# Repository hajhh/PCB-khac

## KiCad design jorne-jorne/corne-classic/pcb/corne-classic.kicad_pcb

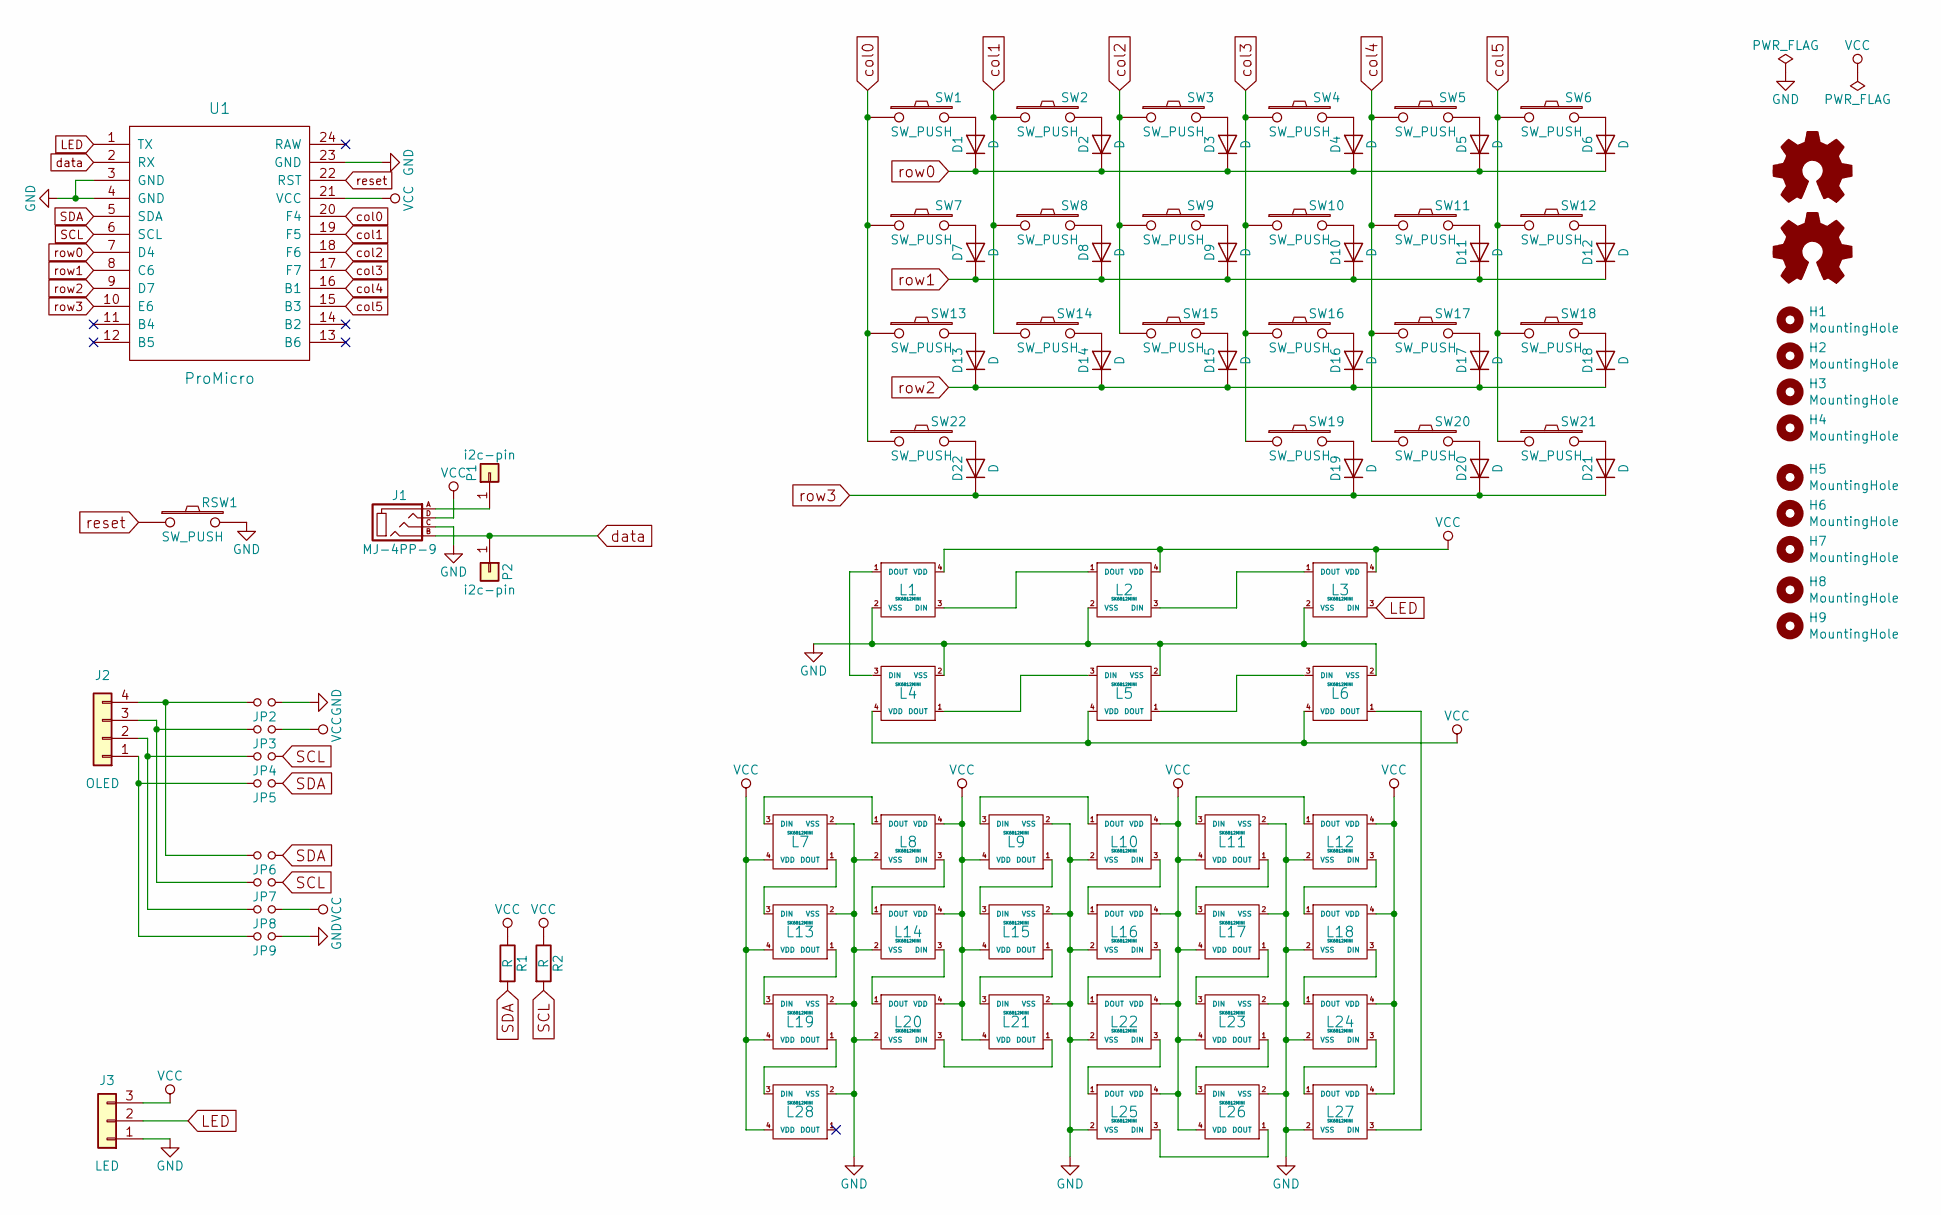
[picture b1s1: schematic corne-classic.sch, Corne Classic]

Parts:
D1, D2, D3, D4, D5, D6, D7, D8, D9, D10, D11, D12, D13, D14, D15, D16, D17, D18, D19, D20, D21, D22: D; D3_TH_SMD
G1, G2: Logo_Open_Hardware_Small; corne
H1, H2, H3, H4, H5, H6, H7, H8, H9: MountingHole; LEGO_HOLE
J1: MJ-4PP-9
J2: OLED
J3: LED; StripLED_rev
JP2, JP3, JP4, JP5, JP6, JP7, JP8, JP9: Jumper
L1, L2, L3, L4, L5, L6: SK6812MINI; SK6812MINI_underglow
L7, L8, L9, L10, L11, L12, L13, L14, L15, L16, L17, L18, L19, L20, L21, L22, L23, L24, L25, L26, L27, L28: SK6812MINI; SK6812MINI_rev
P1, P2: i2c-pin; 1pin_conn
R1, R2: R
RSW1: SW_PUSH; ResetSW
SW1, SW2, SW3, SW4, SW5, SW6, SW7, SW8, SW9, SW10, SW11, SW12, SW13, SW14, SW15, SW16, SW17, SW18, SW19, SW20, SW22: SW_PUSH; MX_ALPS_PG1350_noLed
SW21: SW_PUSH; MX_ALPS_PG1350_noLed_1.75u
U1: ProMicro; ProMicro_v2

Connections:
GND: J1.C, J3.1, JP2.1, JP9.1, L1.2 (VSS), L2.2 (VSS), L3.2 (VSS), L4.2 (VSS), L5.2 (VSS), L6.2 (VSS), L7.2 (VSS), L8.2 (VSS), L9.2 (VSS), L10.2 (VSS), L11.2 (VSS), L12.2 (VSS), L13.2 (VSS), L14.2 (VSS), L15.2 (VSS), L16.2 (VSS), L17.2 (VSS), L18.2 (VSS), L19.2 (VSS), L20.2 (VSS), L21.2 (VSS), L22.2 (VSS), L23.2 (VSS), L24.2 (VSS), L25.2 (VSS), L26.2 (VSS), L27.2 (VSS), L28.2 (VSS), RSW1.2, U1.3 (GND), U1.4 (GND), U1.23 (GND)
LED: J3.2, L3.3 (DIN), U1.1 (TX)
unnamed: D1.2 (A), SW1.2
unnamed: D2.2 (A), SW2.2
unnamed: D3.2 (A), SW3.2
unnamed: D4.2 (A), SW4.2
unnamed: D5.2 (A), SW5.2
unnamed: D6.2 (A), SW6.2
unnamed: D7.2 (A), SW7.2
unnamed: D8.2 (A), SW8.2
unnamed: D9.2 (A), SW9.2
unnamed: D10.2 (A), SW10.2
unnamed: D11.2 (A), SW11.2
unnamed: D12.2 (A), SW12.2
unnamed: D13.2 (A), SW13.2
unnamed: D14.2 (A), SW14.2
unnamed: D15.2 (A), SW15.2
unnamed: D16.2 (A), SW16.2
unnamed: D17.2 (A), SW17.2
unnamed: D18.2 (A), SW18.2
unnamed: D19.2 (A), SW19.2
unnamed: D20.2 (A), SW20.2
unnamed: D21.2 (A), SW21.2
unnamed: D22.2 (A), SW22.2
unnamed: J1.A, P1.1
unnamed: J2.1, JP5.2, JP9.2
unnamed: J2.2, JP4.2, JP8.2
unnamed: J2.3, JP3.2, JP7.2
unnamed: J2.4, JP2.2, JP6.2
unnamed: L1.1 (DOUT), L4.3 (DIN)
unnamed: L1.3 (DIN), L2.1 (DOUT)
unnamed: L2.3 (DIN), L3.1 (DOUT)
unnamed: L4.1 (DOUT), L5.3 (DIN)
unnamed: L5.1 (DOUT), L6.3 (DIN)
unnamed: L7.3 (DIN), L8.1 (DOUT)
unnamed: L9.3 (DIN), L10.1 (DOUT)
unnamed: L10.3 (DIN), L16.1 (DOUT)
unnamed: L11.1 (DOUT), L17.3 (DIN)
unnamed: L11.3 (DIN), L12.1 (DOUT)
unnamed: L12.3 (DIN), L18.1 (DOUT)
unnamed: L13.1 (DOUT), L19.3 (DIN)
unnamed: L7.1 (DOUT), L13.3 (DIN)
unnamed: L8.3 (DIN), L14.1 (DOUT)
unnamed: L14.3 (DIN), L20.1 (DOUT)
unnamed: L15.1 (DOUT), L21.3 (DIN)
unnamed: L9.1 (DOUT), L15.3 (DIN)
unnamed: L16.3 (DIN), L22.1 (DOUT)
unnamed: L17.1 (DOUT), L23.3 (DIN)
unnamed: L18.3 (DIN), L24.1 (DOUT)
unnamed: L19.1 (DOUT), L28.3 (DIN)
unnamed: L20.3 (DIN), L21.1 (DOUT)
unnamed: L22.3 (DIN), L25.1 (DOUT)
unnamed: L23.1 (DOUT), L26.3 (DIN)
unnamed: L24.3 (DIN), L27.1 (DOUT)
unnamed: L25.3 (DIN), L26.1 (DOUT)
unnamed: L6.1 (DOUT), L27.3 (DIN)
SCL: JP4.1, JP7.1, R2.2, U1.6 (SCL)
SDA: JP5.1, JP6.1, R1.2, U1.5 (SDA)
VCC: J1.D, J3.3, JP3.1, JP8.1, L1.4 (VDD), L2.4 (VDD), L3.4 (VDD), L4.4 (VDD), L5.4 (VDD), L6.4 (VDD), L7.4 (VDD), L8.4 (VDD), L9.4 (VDD), L10.4 (VDD), L11.4 (VDD), L12.4 (VDD), L13.4 (VDD), L14.4 (VDD), L15.4 (VDD), L16.4 (VDD), L17.4 (VDD), L18.4 (VDD), L19.4 (VDD), L20.4 (VDD), L21.4 (VDD), L22.4 (VDD), L23.4 (VDD), L24.4 (VDD), L25.4 (VDD), L26.4 (VDD), L27.4 (VDD), L28.4 (VDD), R1.1, R2.1, U1.21 (VCC)
col0: SW1.1, SW7.1, SW13.1, SW22.1, U1.20 (F4)
col1: SW2.1, SW8.1, SW14.1, U1.19 (F5)
col2: SW3.1, SW9.1, SW15.1, U1.18 (F6)
col3: SW4.1, SW10.1, SW16.1, SW19.1, U1.17 (F7)
col4: SW5.1, SW11.1, SW17.1, SW20.1, U1.16 (B1)
col5: SW6.1, SW12.1, SW18.1, SW21.1, U1.15 (B3)
data: J1.B, P2.1, U1.2 (RX)
reset: RSW1.1, U1.22 (RST)
row0: D1.1 (K), D2.1 (K), D3.1 (K), D4.1 (K), D5.1 (K), D6.1 (K), U1.7 (D4)
row1: D7.1 (K), D8.1 (K), D9.1 (K), D10.1 (K), D11.1 (K), D12.1 (K), U1.8 (C6)
row2: D13.1 (K), D14.1 (K), D15.1 (K), D16.1 (K), D17.1 (K), D18.1 (K), U1.9 (D7)
row3: D19.1 (K), D20.1 (K), D21.1 (K), D22.1 (K), U1.10 (E6)

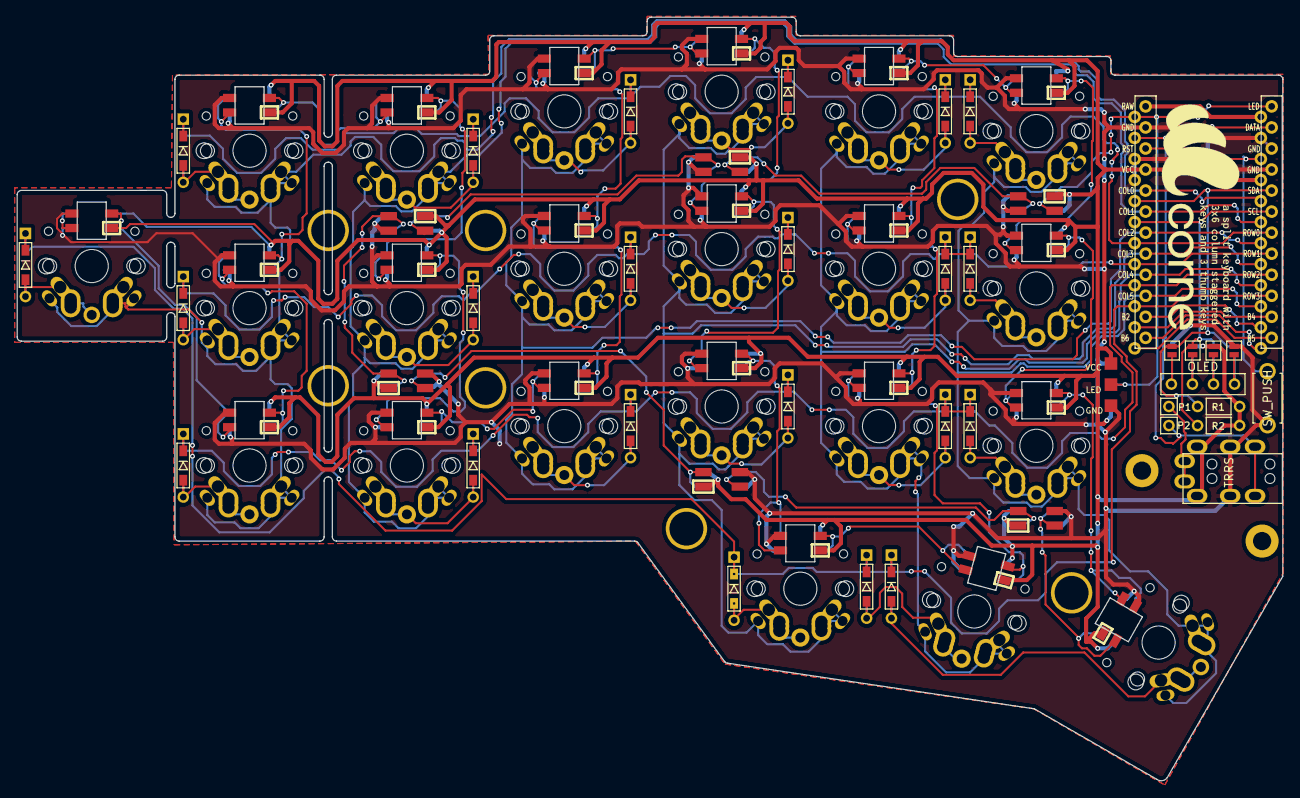
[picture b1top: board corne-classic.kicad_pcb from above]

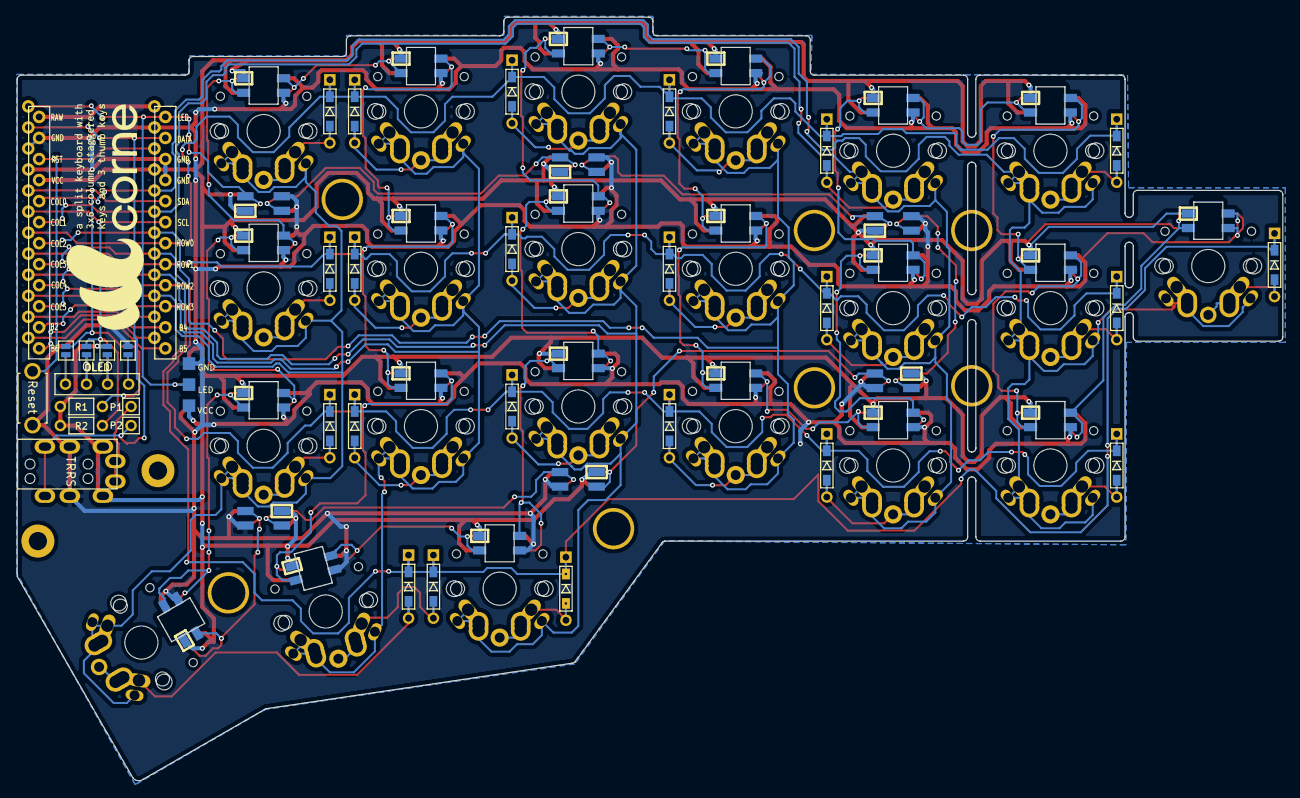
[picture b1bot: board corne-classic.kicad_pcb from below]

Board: 2 copper layers, 152.8 x 92.2 mm, 100 parts (5 on the bottom side), 71 nets.

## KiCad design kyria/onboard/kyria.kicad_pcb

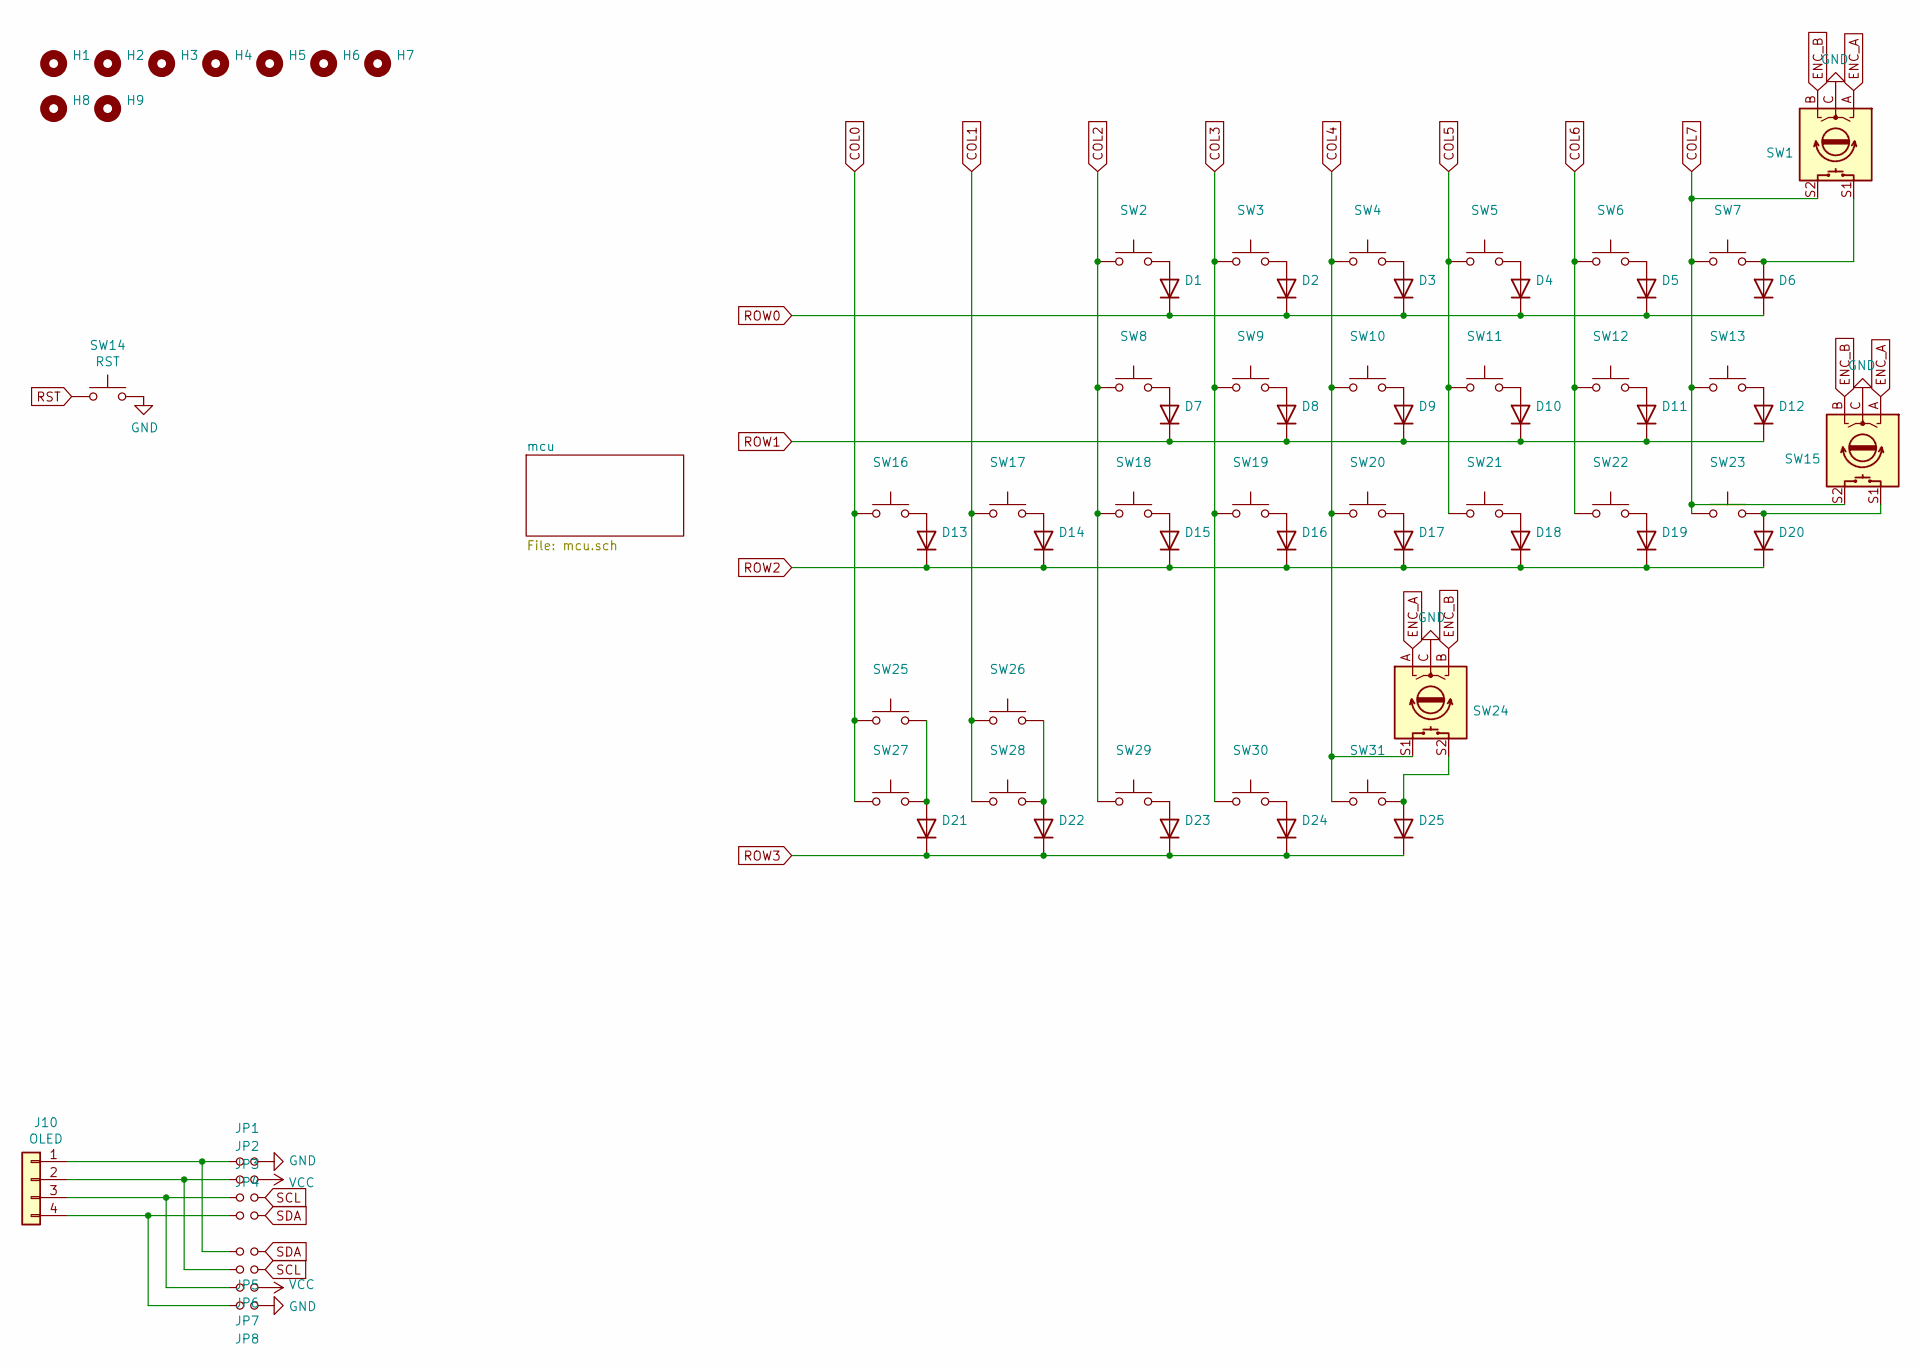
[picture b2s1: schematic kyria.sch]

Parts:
D1, D2, D3, D4, D5, D6, D7, D8, D9, D10, D11, D12, D13, D14, D15, D16, D17, D18, D19, D20, D21, D22, D23, D24, D25: DIODE
H1, H2, H3, H4, H5, H6, H7: Hole
H8, H9: Stab
J10: OLED; 128x64OLED
JP1, JP2, JP3, JP4, JP5, JP6, JP7, JP8: JUMP_NO
SW1, SW15, SW24: ECODER
SW2, SW3, SW4, SW5, SW6, SW7, SW8, SW9, SW10, SW11, SW12, SW13, SW16, SW17, SW18, SW19, SW20, SW21, SW22, SW23, SW25, SW26, SW27, SW28, SW29, SW30, SW31: SW-1u-Aps-Split
SW14: RST; SW_Tactile_SPST_Angled_PTS645Vx31-2LFS

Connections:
COL0: SW16.1, SW25.1, SW27.2; also elsewhere on the board
COL1: SW17.1, SW26.1, SW28.2; also elsewhere on the board
COL2: SW2.1, SW8.1, SW18.1, SW29.1; also elsewhere on the board
COL3: SW3.1, SW9.1, SW19.1, SW30.1; also elsewhere on the board
COL4: SW4.1, SW10.1, SW20.1, SW24.S1, SW31.1; also elsewhere on the board
COL5: SW5.1, SW11.1, SW21.1; also elsewhere on the board
COL6: SW6.1, SW12.1, SW22.1; also elsewhere on the board
COL7: SW1.S2, SW7.2, SW13.2, SW15.S2, SW23.2; also elsewhere on the board
ENC_A: SW1.A, SW15.A, SW24.A; also elsewhere on the board
ENC_B: SW1.B, SW15.B, SW24.B; also elsewhere on the board
GND: JP1.2, JP8.2, SW1.C, SW14.2, SW15.C, SW24.C; also elsewhere on the board
unnamed: D1.2 (A), SW2.2
unnamed: D2.2 (A), SW3.2
unnamed: D3.2 (A), SW4.2
unnamed: D4.2 (A), SW5.2
unnamed: D5.2 (A), SW6.2
unnamed: D6.2 (A), SW1.S1, SW7.1
unnamed: D7.2 (A), SW8.2
unnamed: D8.2 (A), SW9.2
unnamed: D9.2 (A), SW10.2
unnamed: D10.2 (A), SW11.2
unnamed: D11.2 (A), SW12.2
unnamed: D12.2 (A), SW13.1
unnamed: D13.2 (A), SW16.2
unnamed: D14.2 (A), SW17.2
unnamed: D15.2 (A), SW18.2
unnamed: D16.2 (A), SW19.2
unnamed: D17.2 (A), SW20.2
unnamed: D18.2 (A), SW21.2
unnamed: D19.2 (A), SW22.2
unnamed: D20.2 (A), SW15.S1, SW23.1
unnamed: D21.2 (A), SW25.2, SW27.1
unnamed: D22.2 (A), SW26.2, SW28.1
unnamed: D23.2 (A), SW29.2
unnamed: D24.2 (A), SW30.2
unnamed: D25.2 (A), SW24.S2, SW31.2
unnamed: J10.1, JP1.1, JP5.1
unnamed: J10.2, JP2.1, JP6.1
unnamed: J10.3, JP3.1, JP7.1
unnamed: J10.4, JP4.1, JP8.1
ROW0: D1.1 (K), D2.1 (K), D3.1 (K), D4.1 (K), D5.1 (K), D6.1 (K); also elsewhere on the board
ROW1: D7.1 (K), D8.1 (K), D9.1 (K), D10.1 (K), D11.1 (K), D12.1 (K); also elsewhere on the board
ROW2: D13.1 (K), D14.1 (K), D15.1 (K), D16.1 (K), D17.1 (K), D18.1 (K), D19.1 (K), D20.1 (K); also elsewhere on the board
ROW3: D21.1 (K), D22.1 (K), D23.1 (K), D24.1 (K), D25.1 (K); also elsewhere on the board
RST: SW14.1; also elsewhere on the board
SCL: JP3.2, JP6.2; also elsewhere on the board
SDA: JP4.2, JP5.2; also elsewhere on the board
VCC: JP2.2, JP7.2; also elsewhere on the board

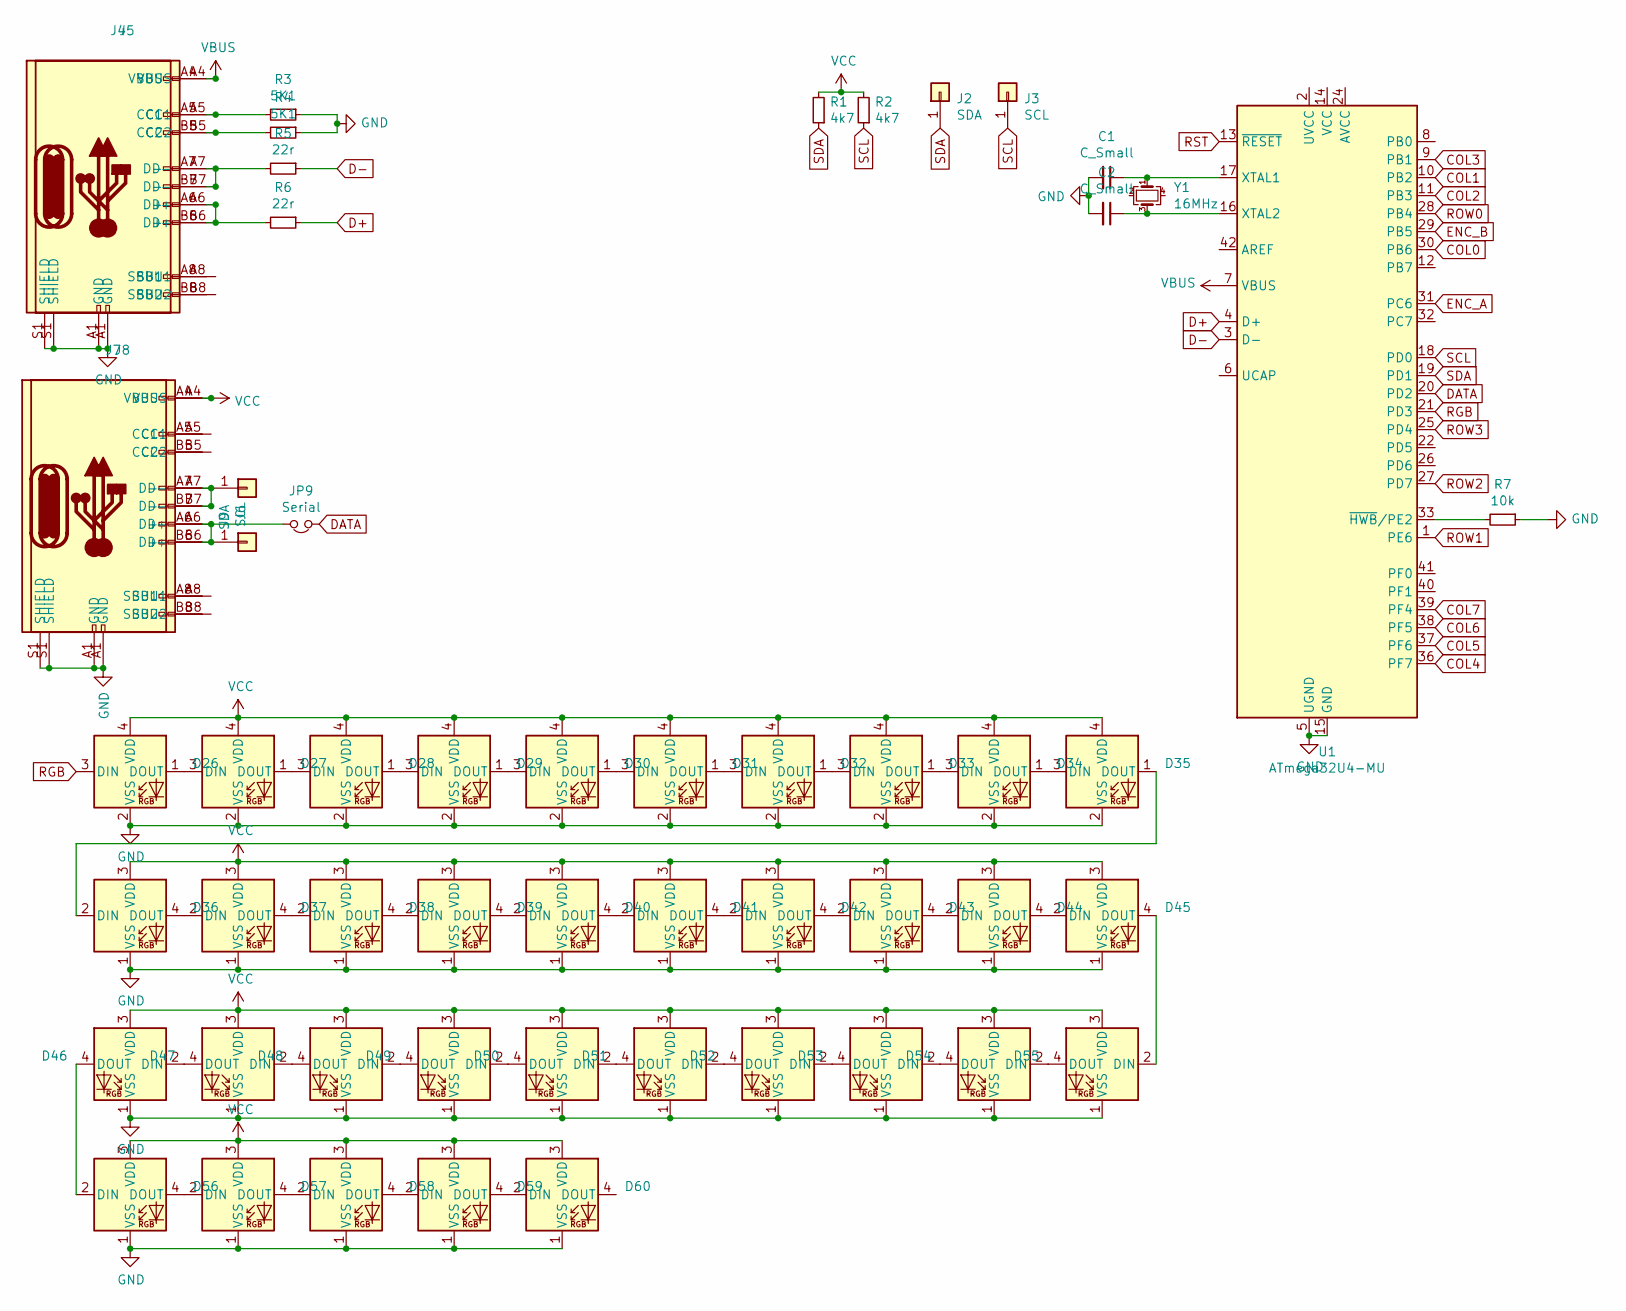
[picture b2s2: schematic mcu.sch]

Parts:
C1, C2: C_Small; C_0603_1608Metric
D26, D27, D28, D29, D30, D31, D32, D33, D34, D35: SK6812MINI-FLIP
D36, D37, D38, D39, D40, D41, D48, D49, D50, D51, D52, D53, D60: sk6812mini-e
D42, D43, D44, D45, D46, D47, D54, D55, D56, D57, D58, D59: sk6812mini-e-r-l
J2, J6: SDA; PinHeader_1x01_P2.00mm_Vertical
J3, J9: SCL; PinHeader_1x01_P2.00mm_Vertical
J4, J5, J7, J8: USB-C-Low
JP9: Serial; JUMP_NO
R1, R2: 4k7; R_0603_1608Metric
R3, R4: 5K1; R_0603_1608Metric
R5, R6: 22r; R_0603_1608Metric
R7: 10k; R_0603_1608Metric
U1: ATmega32U4-MU; QFN-44-1EP_7x7mm_P0.5mm_EP5.2x5.2mm
Y1: 16MHz; Crystal_SMD_2520-4Pin_2.5x2.0mm

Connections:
COL0: U1.30 (PB6); also elsewhere on the board
COL1: U1.10 (PB2); also elsewhere on the board
COL2: U1.11 (PB3); also elsewhere on the board
COL3: U1.9 (PB1); also elsewhere on the board
COL4: U1.36 (PF7); also elsewhere on the board
COL5: U1.37 (PF6); also elsewhere on the board
COL6: U1.38 (PF5); also elsewhere on the board
COL7: U1.39 (PF4); also elsewhere on the board
D+: R6.1, U1.4 (D+)
D-: R5.1, U1.3 (D-)
DATA: JP9.1, U1.20 (PD2)
ENC_A: U1.31 (PC6); also elsewhere on the board
ENC_B: U1.29 (PB5); also elsewhere on the board
GND: C1.2, C2.2, D26.2 (VSS), D27.2 (VSS), D28.2 (VSS), D29.2 (VSS), D30.2 (VSS), D31.2 (VSS), D32.2 (VSS), D33.2 (VSS), D34.2 (VSS), D35.2 (VSS), D36.1 (VSS), D37.1 (VSS), D38.1 (VSS), D39.1 (VSS), D40.1 (VSS), D41.1 (VSS), D42.1 (VSS), D43.1 (VSS), D44.1 (VSS), D45.1 (VSS), D46.1 (VSS), D47.1 (VSS), D48.1 (VSS), D49.1 (VSS), D50.1 (VSS), D51.1 (VSS), D52.1 (VSS), D53.1 (VSS), D54.1 (VSS), D55.1 (VSS), D56.1 (VSS), D57.1 (VSS), D58.1 (VSS), D59.1 (VSS), D60.1 (VSS), J4.A1 (GND), J4.A12 (GND), J4.B1 (GND), J4.B12 (GND), J4.S1 (SHIELD), J5.A1 (GND), J5.A12 (GND), J5.B1 (GND), J5.B12 (GND), J5.S1 (SHIELD), J7.A1 (GND), J7.A12 (GND), J7.B1 (GND), J7.B12 (GND), J7.S1 (SHIELD), J8.A1 (GND), J8.A12 (GND), J8.B1 (GND), J8.B12 (GND), J8.S1 (SHIELD), R3.1, R4.1, R7.1, U1.5 (UGND), U1.15 (GND), U1.23 (GND), U1.35 (GND), U1.43 (GND), U1.45 (GND); also elsewhere on the board
unnamed: C1.1, U1.17 (XTAL1), Y1.1
unnamed: C2.1, U1.16 (XTAL2), Y1.3
unnamed: D26.1 (DOUT), D27.3 (DIN)
unnamed: D27.1 (DOUT), D28.3 (DIN)
unnamed: D28.1 (DOUT), D29.3 (DIN)
unnamed: D29.1 (DOUT), D30.3 (DIN)
unnamed: D30.1 (DOUT), D31.3 (DIN)
unnamed: D31.1 (DOUT), D32.3 (DIN)
unnamed: D32.1 (DOUT), D33.3 (DIN)
unnamed: D33.1 (DOUT), D34.3 (DIN)
unnamed: D34.1 (DOUT), D35.3 (DIN)
unnamed: D35.1 (DOUT), D36.2 (DIN)
unnamed: D36.4 (DOUT), D37.2 (DIN)
unnamed: D37.4 (DOUT), D38.2 (DIN)
unnamed: D38.4 (DOUT), D39.2 (DIN)
unnamed: D39.4 (DOUT), D40.2 (DIN)
unnamed: D40.4 (DOUT), D41.2 (DIN)
unnamed: D41.4 (DOUT), D42.2 (DIN)
unnamed: D42.4 (DOUT), D43.2 (DIN)
unnamed: D43.4 (DOUT), D44.2 (DIN)
unnamed: D44.4 (DOUT), D45.2 (DIN)
unnamed: D45.4 (DOUT), D55.2 (DIN)
unnamed: D46.2 (DIN), D47.4 (DOUT)
unnamed: D46.4 (DOUT), D56.2 (DIN)
unnamed: D47.2 (DIN), D48.4 (DOUT)
unnamed: D48.2 (DIN), D49.4 (DOUT)
unnamed: D49.2 (DIN), D50.4 (DOUT)
unnamed: D50.2 (DIN), D51.4 (DOUT)
unnamed: D51.2 (DIN), D52.4 (DOUT)
unnamed: D52.2 (DIN), D53.4 (DOUT)
unnamed: D53.2 (DIN), D54.4 (DOUT)
unnamed: D54.2 (DIN), D55.4 (DOUT)
unnamed: D56.4 (DOUT), D57.2 (DIN)
unnamed: D57.4 (DOUT), D58.2 (DIN)
unnamed: D58.4 (DOUT), D59.2 (DIN)
unnamed: D59.4 (DOUT), D60.2 (DIN)
unnamed: J4.A5 (CC1), J5.A5 (CC1), R3.2
unnamed: J4.A6 (D+), J4.B6 (D+), J5.A6 (D+), J5.B6 (D+), R6.2
unnamed: J4.A7 (D-), J4.B7 (D-), J5.A7 (D-), J5.B7 (D-), R5.2
unnamed: J4.B5 (CC2), J5.B5 (CC2), R4.2
unnamed: J6.1, J7.A7 (D-), J7.B7 (D-), J8.A7 (D-), J8.B7 (D-)
unnamed: J7.A6 (D+), J7.B6 (D+), J8.A6 (D+), J8.B6 (D+), J9.1, JP9.2
unnamed: R7.2, U1.33 (~HWB~/PE2)
unnamed: U1.14 (VCC), U1.34 (VCC)
unnamed: U1.24 (AVCC), U1.44 (AVCC)
RGB: D26.3 (DIN), U1.21 (PD3)
ROW0: U1.28 (PB4); also elsewhere on the board
ROW1: U1.1 (PE6); also elsewhere on the board
ROW2: U1.27 (PD7); also elsewhere on the board
ROW3: U1.25 (PD4); also elsewhere on the board
RST: U1.13 (~RESET); also elsewhere on the board
SCL: J3.1, R2.1, U1.18 (PD0); also elsewhere on the board
SDA: J2.1, R1.1, U1.19 (PD1); also elsewhere on the board
VBUS: J4.A4 (VBUS), J4.A9 (VBUS), J4.B4 (VBUS), J4.B9 (VBUS), J5.A4 (VBUS), J5.A9 (VBUS), J5.B4 (VBUS), J5.B9 (VBUS), U1.7 (VBUS)
VCC: D26.4 (VDD), D27.4 (VDD), D28.4 (VDD), D29.4 (VDD), D30.4 (VDD), D31.4 (VDD), D32.4 (VDD), D33.4 (VDD), D34.4 (VDD), D35.4 (VDD), D36.3 (VDD), D37.3 (VDD), D38.3 (VDD), D39.3 (VDD), D40.3 (VDD), D41.3 (VDD), D42.3 (VDD), D43.3 (VDD), D44.3 (VDD), D45.3 (VDD), D46.3 (VDD), D47.3 (VDD), D48.3 (VDD), D49.3 (VDD), D50.3 (VDD), D51.3 (VDD), D52.3 (VDD), D53.3 (VDD), D54.3 (VDD), D55.3 (VDD), D56.3 (VDD), D57.3 (VDD), D58.3 (VDD), D59.3 (VDD), D60.3 (VDD), J7.A4 (VBUS), J7.A9 (VBUS), J7.B4 (VBUS), J7.B9 (VBUS), J8.A4 (VBUS), J8.A9 (VBUS), J8.B4 (VBUS), J8.B9 (VBUS), R1.2, R2.2; also elsewhere on the board

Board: 2 copper layers, 129 parts (6 on the bottom side), 98 nets, no tracks yet.

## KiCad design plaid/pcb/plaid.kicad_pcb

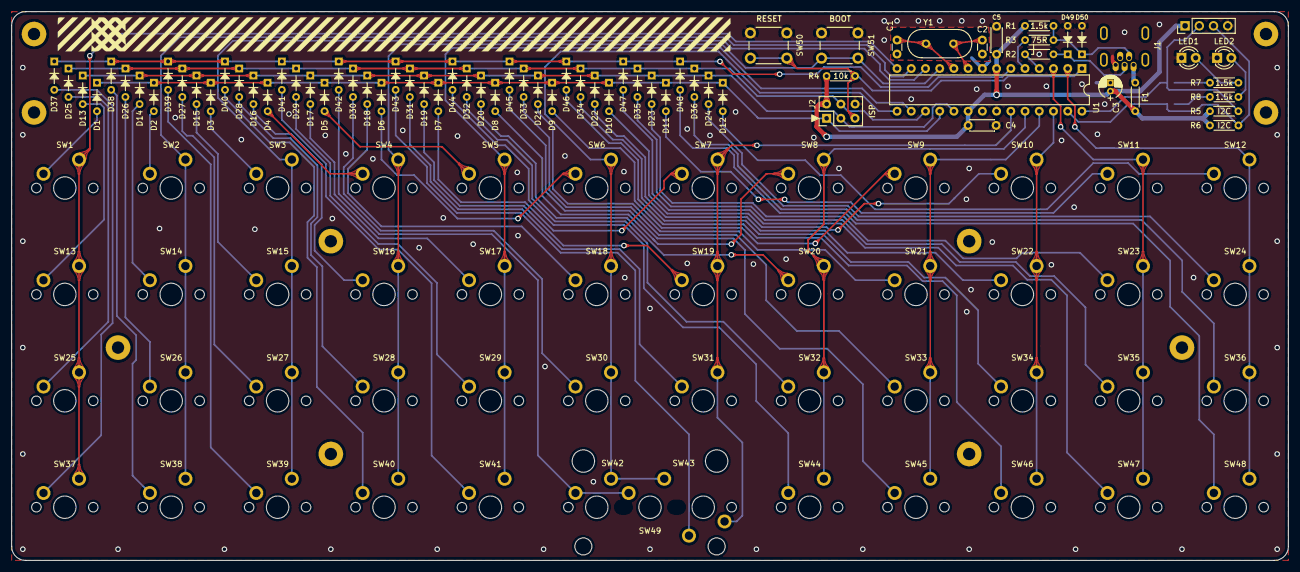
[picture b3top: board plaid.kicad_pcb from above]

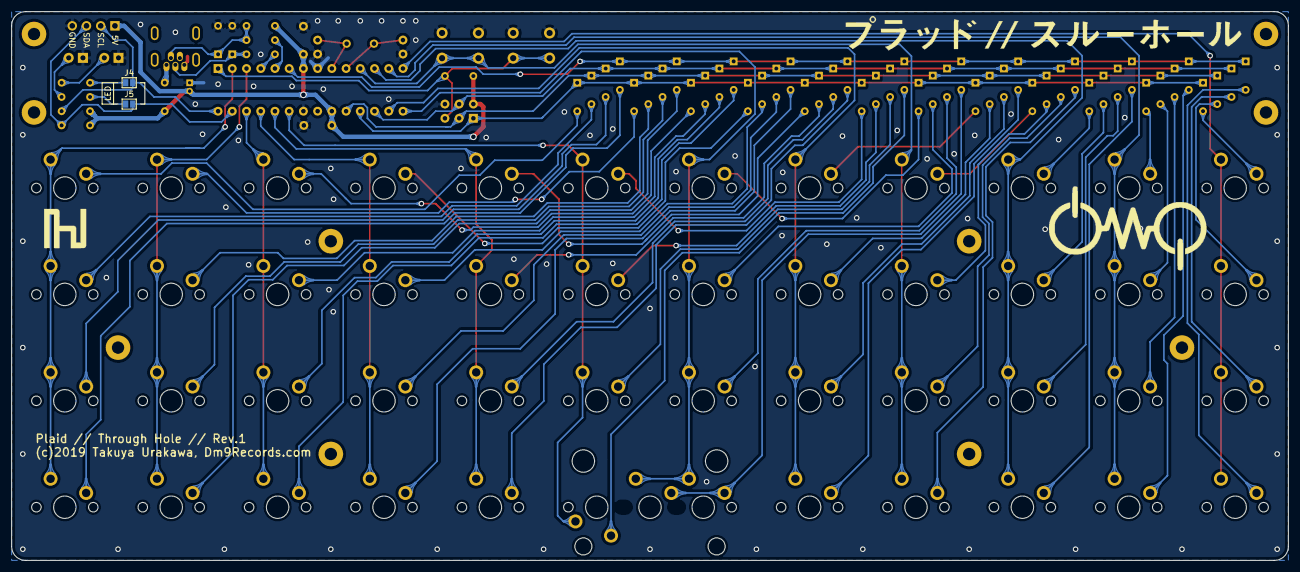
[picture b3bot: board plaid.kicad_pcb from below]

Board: 2 copper layers, 228.0 x 98.0 mm, 134 parts (2 on the bottom side), 80 nets.

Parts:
C1, C2: 20p; C_Disc_D3.0mm_W1.6mm_P2.50mm
C3: 10u; CP_Radial_D4.0mm_P1.50mm
C4, C5: 100n; C_Disc_D4.3mm_W1.9mm_P5.00mm
D1, D2, D3, D4, D5, D6, D7, D8, D9, D10, D11, D12, D13, D14, D15, D16, D17, D18, D19, D20, D21, D22, D23, D24, D25, D26, D27, D28, D29, D30, D31, D32, D33, D34, D35, D36, D37, D38, D39, D40, D41, D42, D43, D44, D45, D46, D47, D48: 1N4148; D_DO-35_SOD27_P5.08mm_Horizontal
D49, D50: 3.6V; D_DO-35_SOD27_P5.08mm_Horizontal
F1: 100mA; polyfuse_5.1mm
H1, H2, H3, H4, H5, H6, H7, H8, H9, H10: M2; MountingHole_2.2mm_M2_Pad
J1: USB_OTG; USB_MINIB_Akizuki_MUSB-5BF01AS
J2: AVR_ISP_6; Pin_Header_Straight_2x03_Pitch2.54mm
J3: Conn_01x04; Pin_Header_Straight_1x04_Pitch2.54mm
J4, J5: GS2
LED1: RED; LED_D3.0mm
LED2: GREEN; LED_D3.0mm
R1, R7, R8: 1.5k; R_Axial_DIN0204_L3.6mm_D1.6mm_P5.08mm_Horizontal
R2, R3: 75R; R_Axial_DIN0204_L3.6mm_D1.6mm_P5.08mm_Horizontal
R4: 10k; R_Axial_DIN0204_L3.6mm_D1.6mm_P5.08mm_Horizontal
R5, R6: I2C; R_Axial_DIN0204_L3.6mm_D1.6mm_P5.08mm_Horizontal
SW1, SW2, SW3, SW4, SW5, SW6, SW7, SW8, SW9, SW10, SW11, SW12, SW13, SW14, SW15, SW16, SW17, SW18, SW19, SW20, SW21, SW22, SW23, SW24, SW25, SW26, SW27, SW28, SW29, SW30, SW31, SW32, SW33, SW34, SW35, SW36, SW37, SW38, SW39, SW40, SW41, SW42, SW43, SW44, SW45, SW46, SW47, SW48: SW_Push; SW_Cherry_MX1A_1.00u_PCB
SW49: SW_Push; SW_Cherry_MX1A_2.0U_PCB_universal_center
SW50: RESET; SW_PUSH_6mm
SW51: BOOT; SW_PUSH_6mm
U1: ATMEGA328-PU; DIP-28_W7.62mm
Y1: 16MHz; Crystal_HC49-4H_Vertical

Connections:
+5V: C3.1, C4.1, C5.1, F1.2, J2.2, J3.1, R1.2, R4.1, R5.1, R6.1, U1.7, U1.20
/COL0: SW1.2, SW13.2, SW25.2, SW37.2, U1.14
/COL1: SW2.2, SW14.2, SW26.2, SW38.2, U1.13
/COL2: SW3.2, SW15.2, SW27.2, SW39.2, U1.12
/COL3: SW4.2, SW16.2, SW28.2, SW40.2, SW51.1, U1.11
/COL4: SW5.2, SW17.2, SW29.2, SW41.2, U1.16
/COL5: SW6.2, SW18.2, SW30.2, SW42.2, SW49.2, U1.15
/COL6: SW7.2, SW19.2, SW31.2, SW43.1, U1.23
/COL7: SW8.2, SW20.2, SW32.2, SW44.2, U1.24
/COL8: SW9.2, SW21.2, SW33.2, SW45.2, U1.25
/COL9: SW10.2, SW22.2, SW34.2, SW46.2, U1.26
/COL10: SW11.2, SW23.2, SW35.2, SW47.2, U1.3
/COL11: SW12.2, SW24.2, SW36.2, SW48.2, U1.2
/RESET: J2.5, R4.2, SW50.1, U1.1
/ROW0: D1.1, D2.1, D3.1, D4.1, D5.1, D6.1, D7.1, D8.1, D9.1, D10.1, D11.1, D12.1, J2.1, U1.18
/ROW1: D13.1, D14.1, D15.1, D16.1, D17.1, D18.1, D19.1, D20.1, D21.1, D22.1, D23.1, D24.1, J2.3, U1.19
/ROW2: D25.1, D26.1, D27.1, D28.1, D29.1, D30.1, D31.1, D32.1, D33.1, D34.1, D35.1, D36.1, J2.4, U1.17
/ROW3: D37.1, D38.1, D39.1, D40.1, D41.1, D42.1, D43.1, D44.1, D45.1, D46.1, D47.1, D48.1, U1.6
/USB_D+: R2.1, U1.4
/USB_D-: R3.1, U1.5
/i2c_SCL: J3.2, J4.2, R5.2, U1.28
/i2c_SDA: J3.3, J5.2, R6.2, U1.27
GND: C1.2, C2.2, C3.2, C4.2, C5.2, D49.2, D50.2, J1.5, J2.6, J3.4, LED1.1, LED2.1, SW50.2, SW51.2, U1.8, U1.22
unnamed: C1.1, U1.10, Y1.2
unnamed: C2.1, U1.9, Y1.1
unnamed: D1.2, SW1.1
unnamed: D2.2, SW2.1
unnamed: D3.2, SW3.1
unnamed: D4.2, SW4.1
unnamed: D5.2, SW5.1
unnamed: D6.2, SW6.1
unnamed: D7.2, SW7.1
unnamed: D8.2, SW8.1
unnamed: D9.2, SW9.1
unnamed: D10.2, SW10.1
unnamed: D11.2, SW11.1
unnamed: D12.2, SW12.1
unnamed: D13.2, SW13.1
unnamed: D14.2, SW14.1
unnamed: D15.2, SW15.1
unnamed: D16.2, SW16.1
unnamed: D17.2, SW17.1
unnamed: D18.2, SW18.1
unnamed: D19.2, SW19.1
unnamed: D20.2, SW20.1
unnamed: D21.2, SW21.1
unnamed: D22.2, SW22.1
unnamed: D23.2, SW23.1
unnamed: D24.2, SW24.1
unnamed: D25.2, SW25.1
unnamed: D26.2, SW26.1
unnamed: D27.2, SW27.1
unnamed: D28.2, SW28.1
unnamed: D29.2, SW29.1
unnamed: D30.2, SW30.1
unnamed: D31.2, SW31.1
unnamed: D32.2, SW32.1
unnamed: D33.2, SW33.1
unnamed: D34.2, SW34.1
unnamed: D35.2, SW35.1
unnamed: D36.2, SW36.1
unnamed: D37.2, SW37.1
unnamed: D38.2, SW38.1
unnamed: D39.2, SW39.1
unnamed: D40.2, SW40.1
unnamed: D41.2, SW41.1
unnamed: D42.2, SW42.1, SW49.1
unnamed: D43.2, SW43.2
unnamed: D44.2, SW44.1
unnamed: D45.2, SW45.1
unnamed: D46.2, SW46.1
unnamed: D47.2, SW47.1
unnamed: D48.2, SW48.1
unnamed: D49.1, J1.3, R2.2
unnamed: D50.1, J1.2, R1.1, R3.2
unnamed: F1.1, J1.1
unnamed: J4.1, R7.1
unnamed: J5.1, R8.1
unnamed: LED1.2, R7.2
unnamed: LED2.2, R8.2

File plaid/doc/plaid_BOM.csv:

Ref,Qty,Value,Description,Vendor
"C1, C2",2,22p,Multi layer ceramic capacitor (2.5mm pitch),
C3,1,4.7u,Electrolytic capacitor (1.5mm pitch),
"C4, C5",2,100n,Multi layer ceramic capacitor (5mm pitch),
D1-48,48,1N4148,General-purpose diode (DO-35),
"D49, D50",2,3.6V Schottky diode,3.6V Schottky diode (DO-35),
F1,1,100mA,Resettable fuse (5mm pitch),
J1,1,USB MINI-B,USB miniB connector,
J2,1,02x03,AVR ISP pin header,
LED1,1,RED,3mm LED,
LED2,1,GREEN,3mm LED,
"R1, R7, R8 ",3,1.5k,1/6W resistor,
"R2, R3",2,75R,1/6W resistor,
R4,1,10k,1/6W resistor,
SW50,1,RESET,6mm tactile switch,
SW51,1,BOOT,6mm tactile switch,
U1,1,ATMEGA328P,,
IC Socket,1,28pin IC Socket,,
Y1,1,16MHz,,
Screw,14,M2 8mm,,
Nut,26,M2,,
Spacer,4,M2 10mm,,
Rubber Feet,4,,,
PCB,1,MAIN PCB,,
PCB,1,BOTTOM PCB,,

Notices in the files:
plaid/pcb/plaid.kicad_pcb:
(c)2019 Takuya Urakawa, Dm9Records.com
